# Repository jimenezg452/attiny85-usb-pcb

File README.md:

------------------------------------
ATtiny85 USB PCB
------------------------------------
KiCad PCB design and manufacturing files for an ATtiny85 USB board.

Project Overview
-

This project is a PCB design created in KiCad as part of my hands-on PCB design and layout learning.

The project includes the KiCad schematic, PCB layout, and manufacturing output files.

Learning Exercise
-
This project was completed as a learning exercise based on an existing YouTube PCB design tutorial.

The purpose of the project was to gain practical experience with:

    KiCad schematic capture
    Component placement
    PCB layout
    Routing
    Design Rule Checking (DRC)
    Footprint assignment and verification
    PCB design organization
    Gerber generation
    Drill-file generation
    Preparing a design for PCB fabrication

This project is intentionally documented as a tutorial-based learning project rather than an independently originated PCB design.

Design Process
-
The project followed the general PCB development workflow:

1. Review the circuit and schematic
2. Assign and verify component footprints
3. Import the design into the PCB Editor
4. Define the board outline
5. Place components
6. Route PCB traces
7. Review clearances and layout
8. Run Design Rule Checking (DRC)
9. Generate manufacturing files
10. Review the resulting Gerber and drill files

Tools
-
    KiCad 9.0
    KiCad Schematic Editor
    KiCad PCB Editor
    KiCad Gerber Viewer

Project Files
-
KiCad Design Files

The repository contains the source design files required to open and inspect the project in KiCad:

    .kicad_pro — KiCad project file
    .kicad_sch — KiCad schematic
    .kicad_pcb — KiCad PCB layout

Manufacturing Files
-
Manufacturing outputs include:

    Gerber files
    Drill files
    PCB fabrication files
    Gerber/drill archive

PCB Design
-
The PCB layout includes:

    Component placement
    Through-hole and/or SMD component footprints as applicable
    Signal routing
    Power routing
    Ground connections
    Board outline
    Silkscreen
    Solder-mask layers

Design Verification
-
The design was reviewed using KiCad's PCB design-rule checking tools.

Verification performed:
    Electrical/PCB Design Rule Check (DRC)
    Footprint verification
    Board outline verification
    Manufacturing file verification
    Gerber review
    Clearance verification

Manufacturing
- 
Gerber and drill files were generated from the KiCad PCB design for the purpose of learning the PCB fabrication workflow.

The manufacturing files are included in this repository for inspection.

Project Status
-
Status: Completed as a learning exercise.

Future work may include independently redesigning or modifying the board to further develop PCB layout and engineering skills.

Future Improvements
-
Potential future revisions may explore:

    Independent component placement
    Alternative routing strategies
    Improved ground/return paths
    Design-for-manufacturing considerations
    Design-rule optimization
    Component substitutions
    PCB layout improvements based on independent analysis

Tutorial / Reference
-
This project was created while following:

Tutorial: KiCAD 7 PCB Layout in 5 steps

Creator: The Circuit Archive

Link: https://www.youtube.com/watch?v=3FGNw28xBr0&list=PLB5qGiy3BHlAJEgiv8YGyFJRMpOSFMpng

Disclaimer
-
This repository represents a personal learning exercise. It should not be considered an independently developed commercial hardware design.

The original tutorial/project creator is credited above.

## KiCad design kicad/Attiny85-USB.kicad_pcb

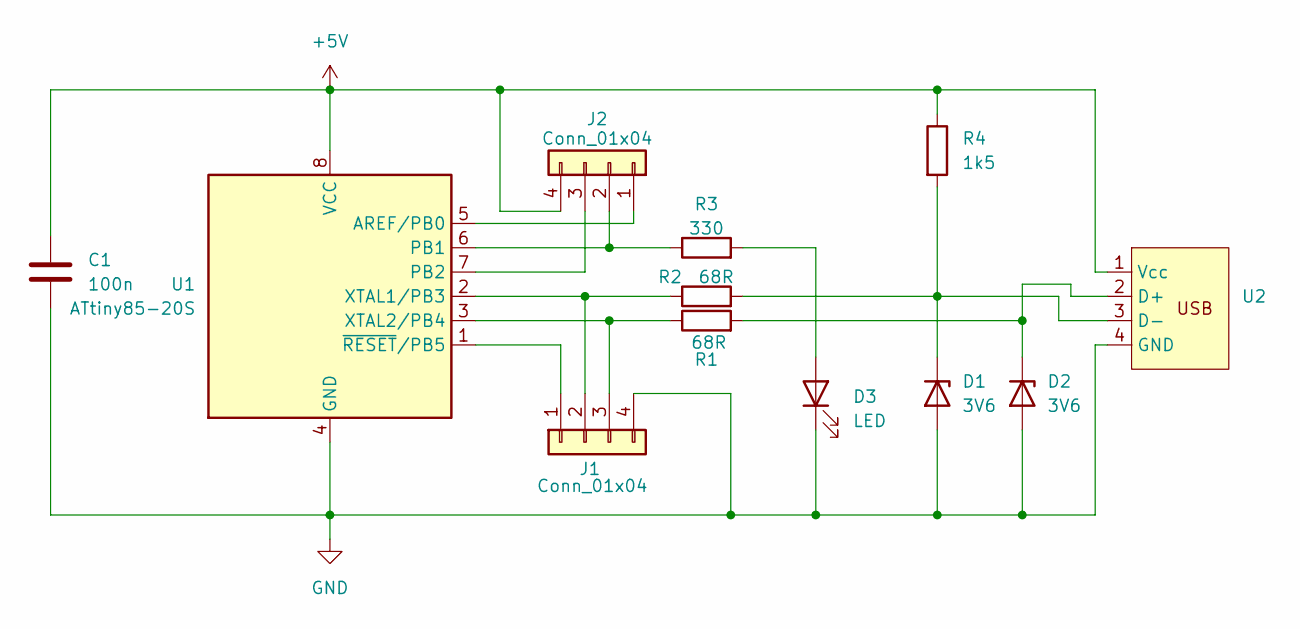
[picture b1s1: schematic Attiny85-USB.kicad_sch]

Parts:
C1: 100n; C_1206_3216Metric_Pad1.33x1.80mm_HandSolder
D1, D2: 3V6; D_SOD-123
D3: LED; LED_D3.0mm
J1, J2: Conn_01x04; PinHeader_1x04_P2.54mm_Vertical
R1, R2: 68R; R_0805_2012Metric_Pad1.20x1.40mm_HandSolder
R3: 330; R_0805_2012Metric_Pad1.20x1.40mm_HandSolder
R4: 1k5; R_0805_2012Metric_Pad1.20x1.40mm_HandSolder
U1: ATtiny85-20S; SOIC-8_5.3x5.3mm_P1.27mm
U2: PCB_USB_Connector

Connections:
+5V: C1.1, J2.4, R4.1, U1.8 (VCC), U2.1 (Vcc)
GND: C1.2, D1.2 (A), D2.2 (A), D3.1 (K), J1.4, U1.4 (GND), U2.4 (GND)
unnamed: D1.1 (K), R2.2, R4.2, U2.3 (D-)
unnamed: D2.1 (K), R1.2, U2.2 (D+)
unnamed: D3.2 (A), R3.2
unnamed: J1.1, U1.1 (~RESET/PB5)
unnamed: J1.2, R2.1, U1.2 (XTAL1/PB3)
unnamed: J1.3, R1.1, U1.3 (XTAL2/PB4)
unnamed: J2.1, U1.5 (AREF/PB0)
unnamed: J2.2, R3.1, U1.6 (PB1)
unnamed: J2.3, U1.7 (PB2)

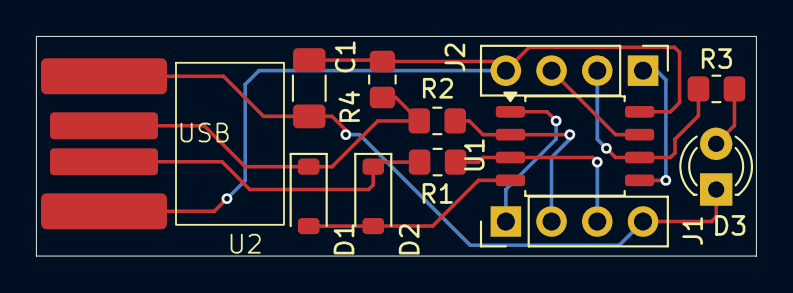
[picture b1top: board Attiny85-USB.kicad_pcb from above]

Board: 2 copper layers, 40.0 x 12.2 mm, 12 parts (0 on the bottom side), 11 nets.
